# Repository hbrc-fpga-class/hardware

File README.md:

# Homebrew Automation Hardware

This repository contains the designs for any physical hardware for the Homebrew Automation PCB.

# tinyfpga-raspi-romi-board
These are the KiCad design files for the PCB. It's designed as follows:

* The Romi chassis needs to have the combined power distribution board and motor controller
* The Romi PDB/MC's onboard regulator **NEEDS TO BE CONFIGURED TO 3.3V OUTPUT OR EVERYTHING WILL BREAK AND YOU WILL BE SAD**
  * This is accomplished by cutting the "VREG Select" trace with an exacto knife. 
* Male headers need to be installed into the following locations (add a picture here....)
  * PWMR / DIRR / nSLPR / GND
  * PWML / DIRL / nSLPL / GND
  * ERA / ERB / GND
  * ELA / ELB / GND
  * 3x VSW / 3x GND
* The custom board should have female headers installed which mate with the male headers on the PDB/MC board
* The raspberry pi and tinyfpga plug into the custom board

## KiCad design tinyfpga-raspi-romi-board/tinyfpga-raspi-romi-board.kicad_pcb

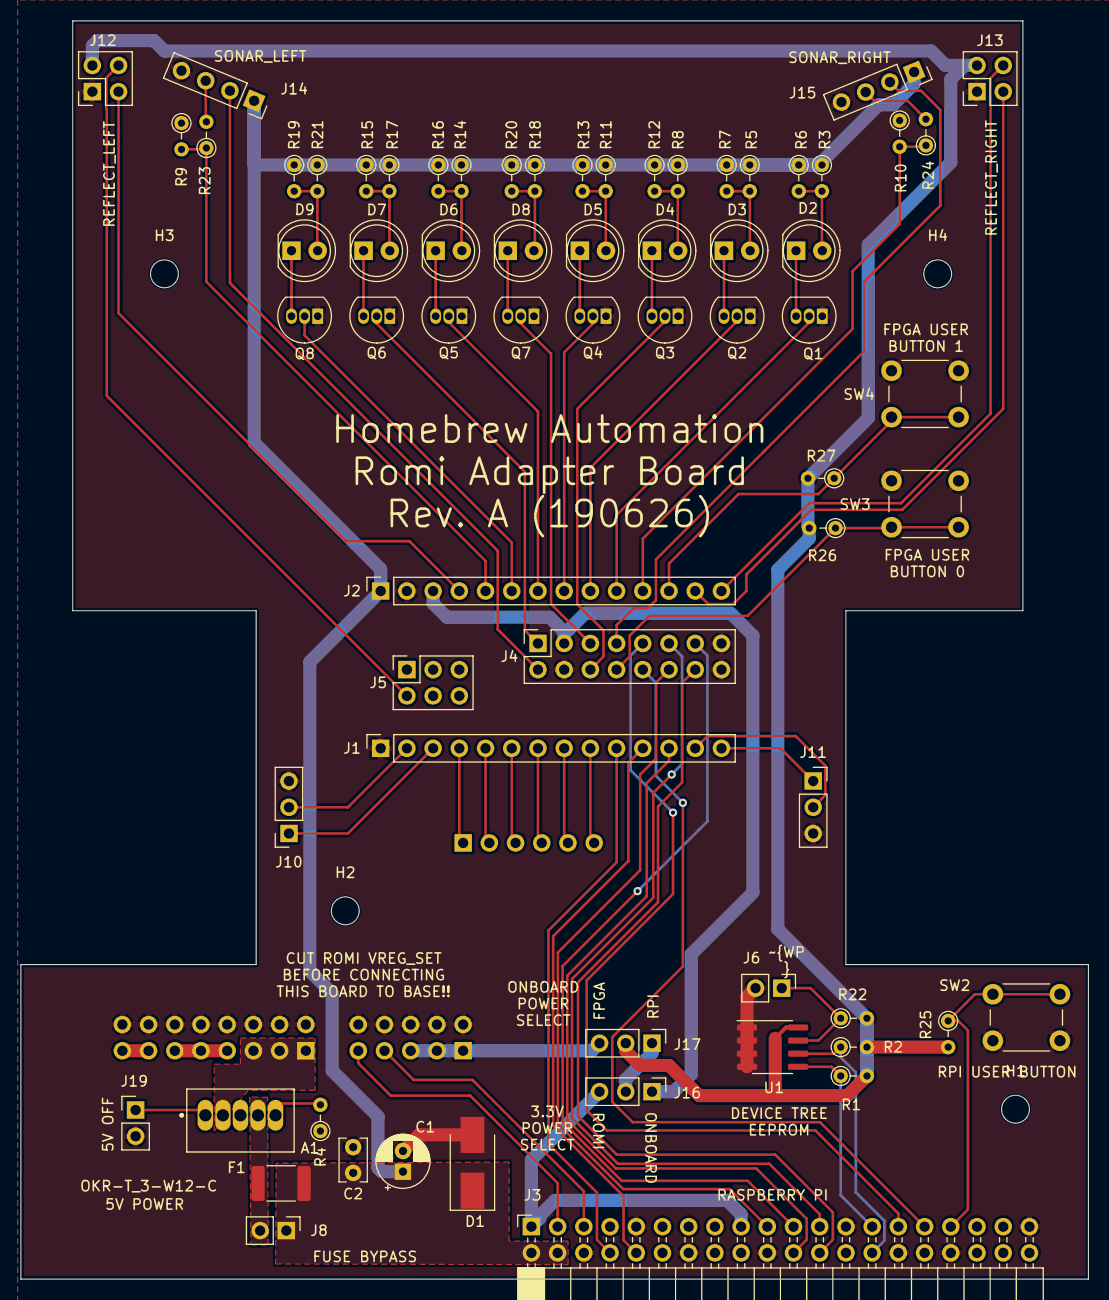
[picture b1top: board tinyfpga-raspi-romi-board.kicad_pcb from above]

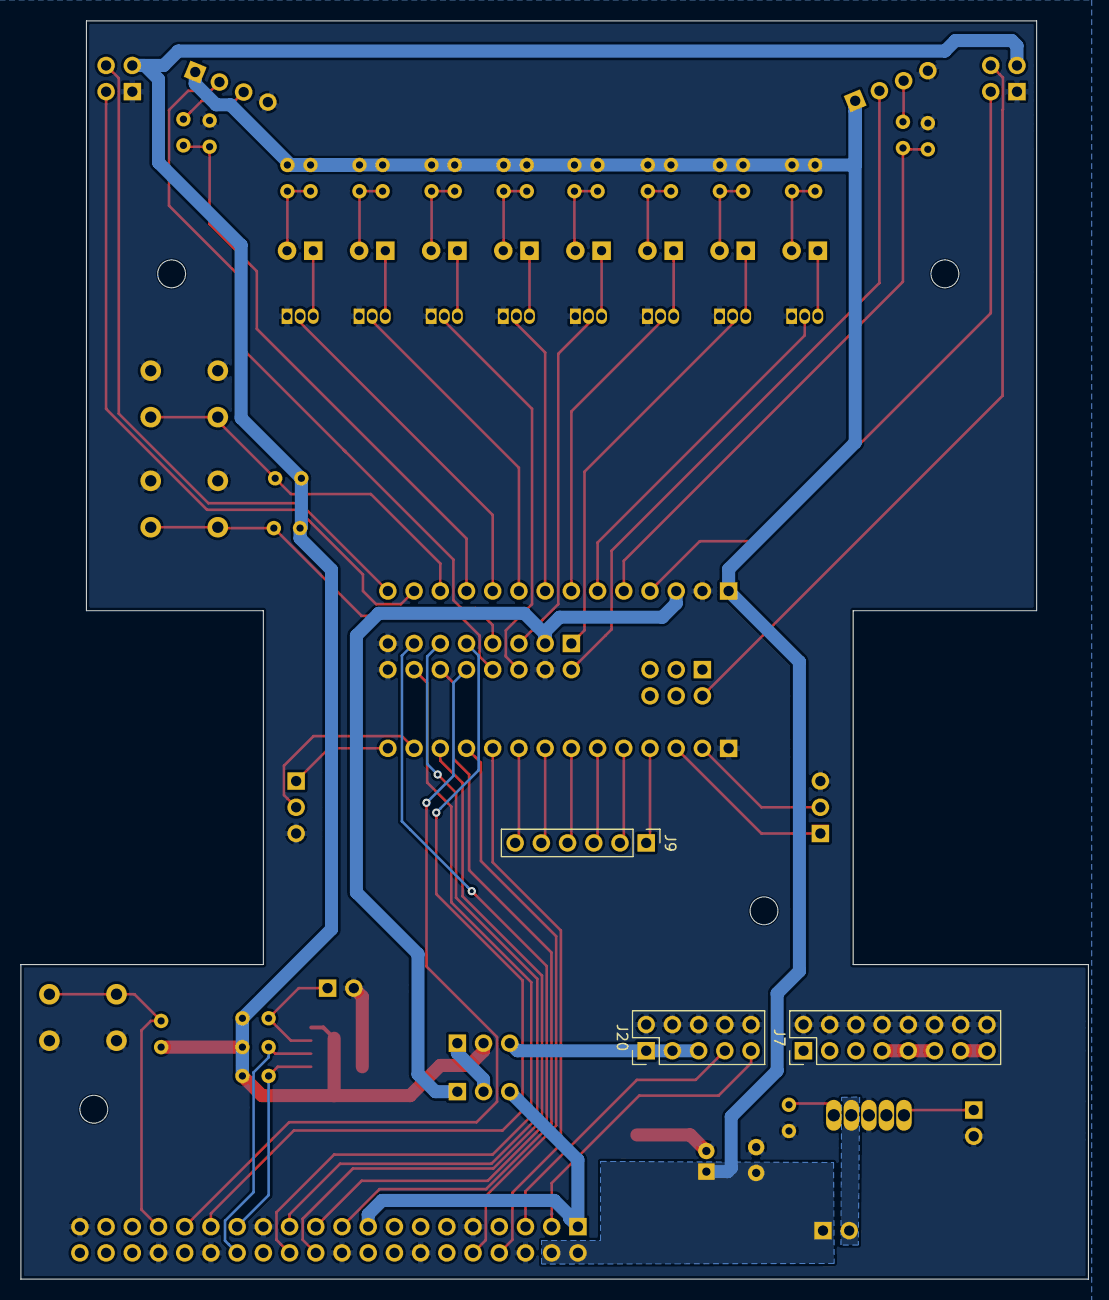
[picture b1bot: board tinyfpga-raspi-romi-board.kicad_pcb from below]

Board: 2 copper layers, 103.4 x 121.9 mm, 75 parts (3 on the bottom side), 74 nets.

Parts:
A1: OKR-T_3-W12-C; Murata_OKR-T-3_P73
C1: 22uF; CP_Radial_D5.0mm_P2.00mm
C2: 1uF; C_Rect_L4.0mm_W2.5mm_P2.50mm
D1: SMBJ5.0A; D_SMB_Handsoldering
D2, D3, D4, D5, D6, D7, D8, D9: LED; LED_D5.0mm_Clear
F1: MF-MSMF250/16X-2; Fuse_1812_4532Metric_Pad1.30x3.40mm_HandSolder
H1, H2, H3, H4: MountingHole; MountingHole_2.7mm_M2.5
J1, J2: Conn_01x14_Female; PinSocket_1x14_P2.54mm_Vertical
J3: Raspberry_Pi_2_3; PinSocket_2x20_P2.54mm_Horizontal
J4: PinSocket_2x08_P2.54mm_Vertical
J5: PinSocket_2x03_P2.54mm_Vertical
J6, J8: PinHeader_1x02_P2.54mm_Vertical
J7: PinHeader_2x08_P2.54mm_Vertical
J9: PinHeader_1x06_P2.54mm_Vertical
J10, J11: PinSocket_1x03_P2.54mm_Vertical
J12, J13: PinSocket_2x02_P2.54mm_Vertical
J14, J15: PinSocket_1x04_P2.54mm_Vertical
J16, J17: PinHeader_1x03_P2.54mm_Vertical
J19: ON_OFF; PinHeader_1x02_P2.54mm_Vertical
J20: PinHeader_2x05_P2.54mm_Vertical
Q1, Q2, Q3, Q4, Q5, Q6, Q7, Q8: 2N7000; TO-92_Inline
R1, R2, R9, R10, R22, R23, R24, R25, R26, R27: 3.9k; R_Axial_DIN0204_L3.6mm_D1.6mm_P2.54mm_Vertical
R3, R4, R5, R6, R7, R8, R11, R12, R13, R14, R15, R16, R17, R18, R19, R20, R21: 268; R_Axial_DIN0204_L3.6mm_D1.6mm_P2.54mm_Vertical
SW2, SW3, SW4: SW_Push; SW_PUSH_6mm_H5mm
U1: CAT24C128; SOIC-8_3.9x4.9mm_P1.27mm

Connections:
+3V3: J12.3, J13.3, J17.2, R1.2, R2.2, R22.2, R25.2, R26.2, R27.2, U1.8
+5V: C1.1, C2.1, D1.1, F1.1, J2.1, J3.2, J3.4, J8.1, J14.1, J15.1, R3.1, R5.1, R6.1, R7.1, R8.1, R11.1, R12.1, R13.1, R14.1, R15.1, R16.1, R17.1, R18.1, R19.1, R20.1, R21.1
+BATT: A1.2, J7.1, J7.3, J7.5
/FPGA_3.3V_OUT: J2.3, J4.3, J16.1
/FPGA_BTN0: J4.8, R26.1, SW3.2
/FPGA_BTN1: J2.12, R27.1, SW4.2
/FPGA_HBA_INT: J1.12, J3.22
/FPGA_LED0: J2.10, Q1.2
/FPGA_LED1: J4.6, Q3.2
/FPGA_LED2: J2.7, Q5.2
/FPGA_LED3: J4.5, Q7.2
/FPGA_LED4: J2.9, Q2.2
/FPGA_LED5: J2.8, Q4.2
/FPGA_LED6: J4.1, Q6.2
/FPGA_LED7: J2.6, Q8.2
/FPGA_SCK: J3.23, J4.11
/FPGA_SDI: J3.19, J4.12
/FPGA_SDO: J3.21, J4.13
/FPGA_SS: J3.24, J4.14
/FPGA_~HOLD: J3.29, J4.9
/FPGA_~WP: J3.31, J4.10
/QTRL_CTRL: J5.2, J12.4
/QTRL_OUT: J2.4, J12.2
/QTRR_CTRL: J2.14, J13.4
/QTRR_OUT: J2.13, J13.2
/ROMI_3V3: J17.3, J20.1, J20.3, J20.5
/ROMI_DIRL: J1.5, J9.2
/ROMI_DIRR: J1.8, J9.5
/ROMI_ENC_LA: J1.3, J10.1
/ROMI_ENC_LB: J1.2, J10.2
/ROMI_ENC_RA: J1.14, J11.1
/ROMI_ENC_RB: J1.13, J11.2
/ROMI_PG: J3.5, J20.7
/ROMI_PWML: J1.6, J9.3
/ROMI_PWMR: J1.9, J9.6
/ROMI_SHDN: J3.3, J20.9
/ROMI_~SLPL: J1.4, J9.1
/ROMI_~SLPR: J1.7, J9.4
/RPI_3.3V_OUT: J3.1, J3.17, J16.3
/RPI_BTN0: J3.33, R25.1, SW2.2
/RPI_ID_SC: J3.28, R2.1, U1.6
/RPI_ID_SD: J3.27, R1.1, U1.5
/RPI_RXD: J1.11, J3.10
/RPI_TXD: J1.10, J3.8
/SONL_ECHO: J2.5, R9.2, R23.1
/SONL_TRIG: J4.2, J14.2
/SONR_ECHO: J2.11, R10.2, R24.1
/SONR_TRIG: J4.7, J15.2
/VB: J7.13, J7.15
/VREG_OUT: A1.4, F1.2, J8.2
/VRP: J7.7, J7.9, J7.11
GND: A1.3, C1.2, C2.2, D1.2, J1.1, J2.2, J3.6, J3.9, J3.14, J3.20, J3.25, J3.30, J3.34, J3.39, J4.4, J4.15, J4.16, J6.2, J7.2, J7.4, J7.6, J7.8, J7.10, J7.12, J7.14, J7.16, J10.3, J11.3, J12.1, J13.1, J14.4, J15.4, J19.2, J20.2, J20.4, J20.6, J20.8, J20.10, Q1.1, Q2.1, Q3.1, Q4.1, Q5.1, Q6.1, Q7.1, Q8.1, R4.1, R9.1, R10.1, SW2.1, SW3.1, SW4.1, U1.1, U1.2, U1.3, U1.4
unnamed: A1.1, J19.1
unnamed: A1.5, R4.2
unnamed: D2.1, Q1.3
unnamed: D2.2, R3.2, R6.2
unnamed: D3.1, Q2.3
unnamed: D3.2, R5.2, R7.2
unnamed: D4.1, Q3.3
unnamed: D4.2, R8.2, R12.2
unnamed: D5.1, Q4.3
unnamed: D5.2, R11.2, R13.2
unnamed: D6.1, Q5.3
unnamed: D6.2, R14.2, R16.2
unnamed: D7.1, Q6.3
unnamed: D7.2, R15.2, R17.2
unnamed: D8.1, Q7.3
unnamed: D8.2, R18.2, R20.2
unnamed: D9.1, Q8.3
unnamed: D9.2, R19.2, R21.2
unnamed: J6.1, R22.1, U1.7
unnamed: J14.3, R23.2
unnamed: J15.3, R24.2
unnamed: J16.2, J17.1

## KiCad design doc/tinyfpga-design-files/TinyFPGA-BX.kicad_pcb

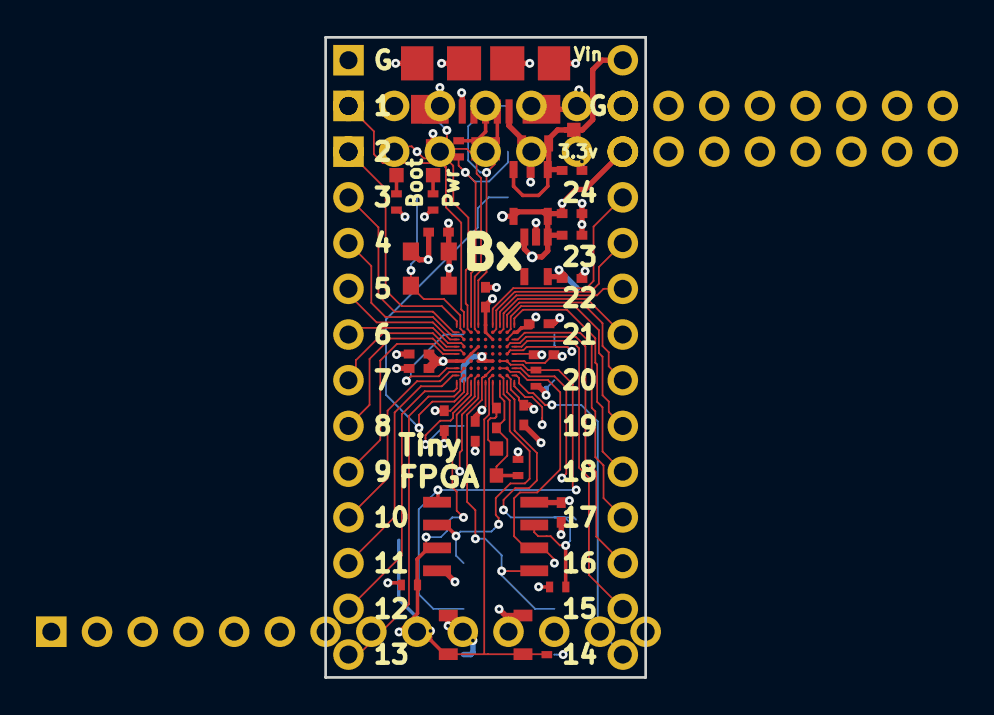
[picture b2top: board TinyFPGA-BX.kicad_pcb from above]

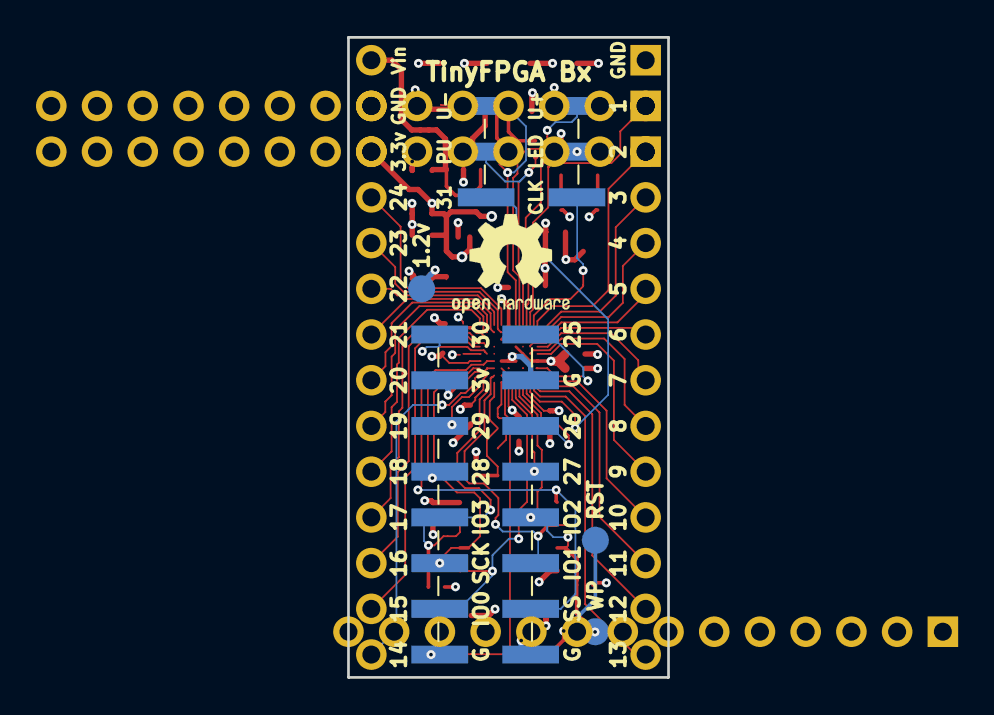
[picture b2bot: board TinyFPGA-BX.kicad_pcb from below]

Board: 4 copper layers, 17.8 x 35.6 mm, 47 parts (5 on the bottom side), 54 nets.

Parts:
C1, C2, C3, C4: 1uF; C_0402_NoSilk
C5, C7, C8, C9, C10, C11, C16: 100nF; C_0402_NoSilk
C6, C17: 10uF; C_0603
C12, C13, C14, C15: 10nF; C_0402_NoSilk
D1, D2: LED_Small; LED_0603
J1, J1#2, J1#3, J1#4, J2: CONN_01X14; Pin_Header_Straight_1x14_Pitch2.54mm
J3: USB_OTG; USB_Micro-B_Molex_47346-0001
J4: Conn_02x08_Odd_Even; Pin_Header_Straight_2x08_Pitch2.54mm_SMD
J5: Conn_02x03_Odd_Even; Pin_Header_Straight_2x03_Pitch2.54mm_SMD
L1: Bead; L_0603
R1: 1.5k; R_0402_NoSilk
R2, R3: 68; R_0402_NoSilk
R4: 100; R_0402_NoSilk
R5, R7, R10: 10k; R_0402_NoSilk
R6: R; R_0402
R8, R9: 270; R_0402_NoSilk
SW1: SW_Push; PTS_810_SMT_Switch
TP1, TP2, TP3: TEST; Measurement_Point_Round-SMD-Pad_Small
U1: iCE40-LP8K-CM81; CM81
U2: MIC5504-3.3YM5-TR; SC-70-C5
U3: DSC6001CI2A-016.0000T; CDFN3225-4LD-PL-1
U4: MIC5365-1.2YC5-TR; SC-70-C5
U5: AT25SF081-SSHD-B; SOIC-8_3.9x4.9mm_Pitch1.27mm

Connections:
2A: J1#4.5, U1.C2
3A: J1#4.4, U1.B1
3B: J1#4.6, U1.C1
7A: J1#4.7, U1.D2
10A: J1#4.8, U1.D1
10B: J1#4.10, U1.E1
13A: J1#4.9, U1.E2
24B: J4.2, U1.G1
26A: J1#4.11, U1.G2
26B: J1#4.14, U1.H2
54: J1#4.12, U1.H1
55: J1#4.13, U1.J1
56: J5.2, U1.J2
57: J4.6, U1.J3
70: J4.8, U1.J4
82: J4.10, R7.2, TP1.1, U1.H4, U5.3
109: J4.9, R10.2, U1.J8, U5.7
110: J4.5, U1.J9
111: J2.14, U1.H9
112: J4.7, U1.G9
116: J2.10, U1.A9
119: J2.13, U1.D9
140: J4.1, U1.E8
141: J2.12, U1.D8
148: J2.11, U1.C9
170: J2.9, U1.B8
174: J2.8, U1.A8
177: J2.6, U1.A7
180: J2.7, U1.B7
183: J2.5, U1.B6
185: J2.4, U1.A6
221: J1#4.2, U1.A2
224: J1#4.3, U1.A1
+1V2: C3.1, C11.1, C12.1, C13.1, R4.2, TP3.1, U1.D4, U1.E3, U1.E9, U1.F1, U1.F2, U4.5
+3V3: C2.1, C4.1, C5.1, C8.1, C9.1, C10.1, C14.1, C15.1, C16.1, D1.2, J2.3, J4.3, R5.1, R6.1, R7.1, R10.1, U1.A5, U1.B5, U1.B9, U1.C6, U1.C8, U1.H3, U1.H8, U1.J5, U2.4, U2.5, U3.1, U3.4, U4.1, U4.3, U5.8
+5V: C1.1, C17.1, J2.1, L1.1, U2.1, U2.3
CLK: J5.1, U1.B2, U3.3
CRESET_B: R6.2, SW1.2, TP2.1, U1.H6
GND: C1.2, C2.2, C3.2, C4.2, C5.2, C8.2, C9.2, C10.2, C11.2, C12.2, C13.2, C14.2, C15.2, C16.2, C17.2, J1#4.1, J2.2, J3.5, J3.6, J4.4, J4.15, J4.16, R8.2, R9.2, SW1.1, U1.E4, U1.E5, U1.F4, U1.F5, U1.F6, U1.F9, U2.2, U3.2, U4.2, U5.4
LED: D2.2, J5.3, U1.B3
unnamed: C6.1, C7.1, U1.J6
unnamed: C6.2, C7.2, R4.1, U1.J7
unnamed: D1.1, R8.1
unnamed: D2.1, R9.1
unnamed: J3.1, L1.2
unnamed: J3.2, R3.2
unnamed: J3.3, R1.1, R2.2
SCK: J4.11, U1.G7, U1.G8, U5.6
SDI: J4.12, U1.H7, U5.2
SDO: J4.13, U1.G6, U1.H5, U5.5
SS: J4.14, R5.2, U1.F7, U1.F8, U5.1
USB_N: J5.6, R3.1, U1.A4
USB_P: J5.5, R2.1, U1.B4
USB_PU: J5.4, R1.2, U1.A3

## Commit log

2019-05-06 initial commit with board files and mech
2019-05-13 added more to schem, notably the 5v TH reg
2019-05-14 provided a preliminary how-it-should-work description
2019-05-14 Added all headers connnecting the custom board to the romi pdb-mc board
2019-05-14 I don't want a module, I just want the design files
2019-05-14 annotated the parts. woah. big change
2019-05-14 added sensor connectors. wired more or less everything together. broke out FPGA SPI flash pins
2019-05-14 Added schematic for reference
2019-05-14 fixing submodule path
2019-05-22 organization and labeling of hardware block
2019-05-30 added some formatting for pres
2019-06-03 contains info about supplier modules. digikey bom to come later
2019-06-03 reorganized hw directory
2019-06-03 added leds and user buttons. needs to be refactored to more sheets
2019-06-04 cluttered and gross... JUST THE WAY I LIKE IT
2019-06-05 finally got footprints on a board. starting arranging them
2019-06-05 kicad crashed but work was recovered. don't need autosave
2019-06-11 imported mech drawings to kicad pcb for placement
2019-06-11 made some minor tweaks and measured tinypcb with headers
2019-06-13 Everything fits on a board
2019-06-13 All components placed on board. Needs routing doe
2019-06-14 Spaced out componenets more
2019-06-18 oh hey look its all through hole
2019-06-20 updated mechanical dimensions, moved power and buttons
2019-06-20 incorporated some of wayne and brandons adjustements
2019-06-20 removed the rescue files because FUCK IT THAT'S WHY
2019-06-24 happy with power section
2019-06-24 happy with mechanicals. routing and pin swapping
2019-06-24 mostly done routing but have a few more rpi signals to deal with
2019-06-24 signals routed. needs silk and drc
2019-06-24 changed mount hole size and aligned them better. added pwm pulldowns
2019-06-26 rev-a sent to fab
2019-06-30 updated schematic and PDF
2019-07-02 cleaned up bom
2019-07-02 moved bom into build
2019-07-02 minor README update to test development branch creation
2019-07-08 added reworks doc
2019-07-22 Add couple more rework notes
2019-07-22 pulldown resistor ineffective. disabling feature instead
2019-07-23 suggestion to potentially prevent RPI undervolting
2019-07-25 updated schem
2019-07-25 changing name to be errata and nice to haves
2019-08-01 moved errata and issues to github
2019-08-01 minor readme changes
2019-08-01 moved outputs out of main project folder
2019-08-01 reorganization and renaming of hardware
2019-08-01 keeping old bom files for reference (temporarily) but renaming to differentiate them from new ones
